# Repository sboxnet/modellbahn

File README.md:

# modellbahn

A project to supply code for my modellrailway.

Contains:
    
<h2>avr</h2>
code for ATMEL Microcontroller atxmega32a4u: Booster, Gleisbesetztmelder, Weichenservo, DCC Generator
<h2>kicad</h2>
schemas und layouts
<h2>libtmb++</h2>
library for programmer
<h2>programmer</h2>
programmer to program atmel xmega mcu's over PDI

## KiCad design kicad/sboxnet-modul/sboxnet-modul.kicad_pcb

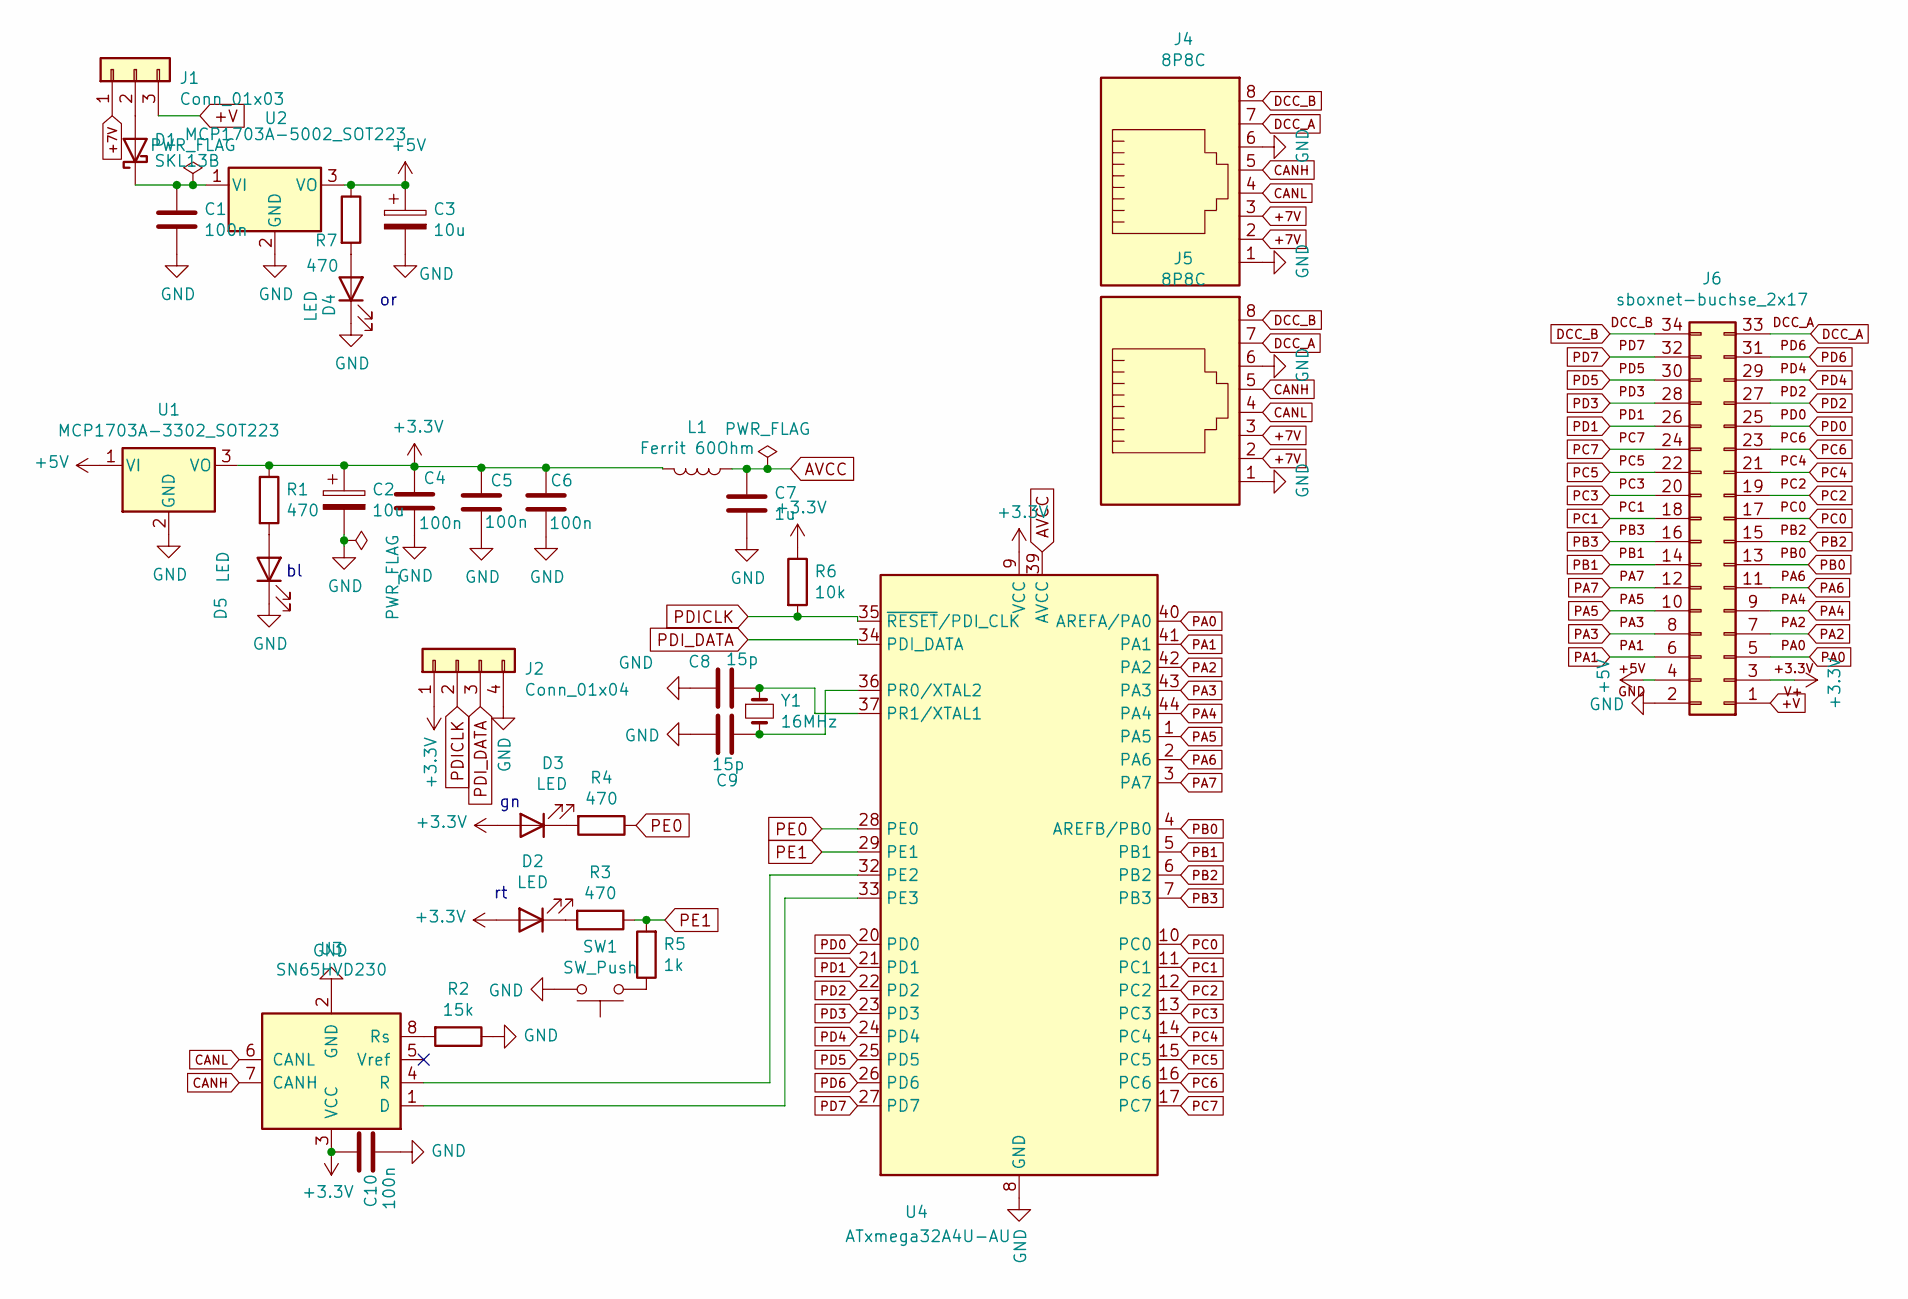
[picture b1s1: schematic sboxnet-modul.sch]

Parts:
C1, C4, C5, C6, C10: 100n; C_1206_3216Metric_Pad1.42x1.75mm_HandSolder
C2: 10u; C_1206_3216Metric_Pad1.42x1.75mm_HandSolder
C3: 10u; C_1206_3216Metric
C7: 1u; C_1206_3216Metric_Pad1.42x1.75mm_HandSolder
C8, C9: 15p; C_1206_3216Metric_Pad1.42x1.75mm_HandSolder
D1: SKL13B; D_SMB_Handsoldering
D2, D3, D4, D5: LED; LED_1206_3216Metric_Pad1.42x1.75mm_HandSolder
J1: Conn_01x03; PinHeader_1x03_P2.54mm_Vertical
J2: Conn_01x04; PinSocket_1x04_P2.54mm_Vertical
J4, J5: 8P8C; 8p8c-mebp
J6: sboxnet-buchse_2x17; sboxnet-buchse-2x17
L1: Ferrit 60Ohm; L_1206_3216Metric_Pad1.42x1.75mm_HandSolder
R1, R3, R4, R7: 470; R_1206_3216Metric_Pad1.42x1.75mm_HandSolder
R2: 15k; R_1206_3216Metric_Pad1.42x1.75mm_HandSolder
R5: 1k; R_1206_3216Metric_Pad1.42x1.75mm_HandSolder
R6: 10k; R_1206_3216Metric_Pad1.42x1.75mm_HandSolder
SW1: SW_Push; JTP-1130
U1: MCP1703A-3302_SOT223; SOT-223-3_TabPin2
U2: MCP1703A-5002_SOT223; SOT-223-3_TabPin2
U3: SN65HVD230; SOIC-8_3.9x4.9mm_P1.27mm
U4: ATxmega32A4U-AU; TQFP-44_10x10mm_P0.8mm
Y1: 16MHz; Crystal_HC49-U_Vertical

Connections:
+3V3: C2.1, C4.2, C5.2, C6.2, C10.2, D2.2 (A), D3.2 (A), J2.1, J6.3, L1.2, R1.1, R6.1, U1.3 (VO), U3.3 (VCC), U4.9 (VCC), U4.19 (VCC), U4.31 (VCC)
+5V: C3.1, J6.4, R7.1, U1.1 (VI), U2.3 (VO)
+7V: J1.1, J4.2, J4.3, J5.2, J5.3
+V: J1.3, J6.1
AVCC: C7.2, L1.1, U4.39 (AVCC)
CANH: J4.5, J5.5, U3.7 (CANH)
CANL: J4.4, J5.4, U3.6 (CANL)
DCC_A: J4.7, J5.7, J6.33
DCC_B: J4.8, J5.8, J6.34
GND: C1.1, C2.2, C3.2, C4.1, C5.1, C6.1, C7.1, C8.2, C9.2, C10.1, D4.1 (K), D5.1 (K), J2.4, J4.1, J4.6, J5.1, J5.6, J6.2, R2.1, SW1.2, U1.2 (GND), U2.2 (GND), U3.2 (GND), U4.8 (GND), U4.18 (GND), U4.30 (GND), U4.38 (GND)
unnamed: C1.2, D1.1 (K), U2.1 (VI)
unnamed: C8.1, U4.37 (PR1/XTAL1), Y1.1
unnamed: C9.1, U4.36 (PR0/XTAL2), Y1.2
unnamed: D1.2 (A), J1.2
unnamed: D2.1 (K), R3.2
unnamed: D3.1 (K), R4.2
unnamed: D4.2 (A), R7.2
unnamed: D5.2 (A), R1.2
unnamed: R2.2, U3.8 (Rs)
unnamed: R5.1, SW1.1
unnamed: U3.1 (D), U4.33 (PE3)
unnamed: U3.4 (R), U4.32 (PE2)
PA0: J6.5, U4.40 (AREFA/PA0)
PA1: J6.6, U4.41 (PA1)
PA2: J6.7, U4.42 (PA2)
PA3: J6.8, U4.43 (PA3)
PA4: J6.9, U4.44 (PA4)
PA5: J6.10, U4.1 (PA5)
PA6: J6.11, U4.2 (PA6)
PA7: J6.12, U4.3 (PA7)
PB0: J6.13, U4.4 (AREFB/PB0)
PB1: J6.14, U4.5 (PB1)
PB2: J6.15, U4.6 (PB2)
PB3: J6.16, U4.7 (PB3)
PC0: J6.17, U4.10 (PC0)
PC1: J6.18, U4.11 (PC1)
PC2: J6.19, U4.12 (PC2)
PC3: J6.20, U4.13 (PC3)
PC4: J6.21, U4.14 (PC4)
PC5: J6.22, U4.15 (PC5)
PC6: J6.23, U4.16 (PC6)
PC7: J6.24, U4.17 (PC7)
PD0: J6.25, U4.20 (PD0)
PD1: J6.26, U4.21 (PD1)
PD2: J6.27, U4.22 (PD2)
PD3: J6.28, U4.23 (PD3)
PD4: J6.29, U4.24 (PD4)
PD5: J6.30, U4.25 (PD5)
PD6: J6.31, U4.26 (PD6)
PD7: J6.32, U4.27 (PD7)
PDICLK: J2.2, R6.2, U4.35 (~RESET~/PDI_CLK)
PDI_DATA: J2.3, U4.34 (PDI_DATA)
PE0: R4.1, U4.28 (PE0)
PE1: R3.1, R5.2, U4.29 (PE1)

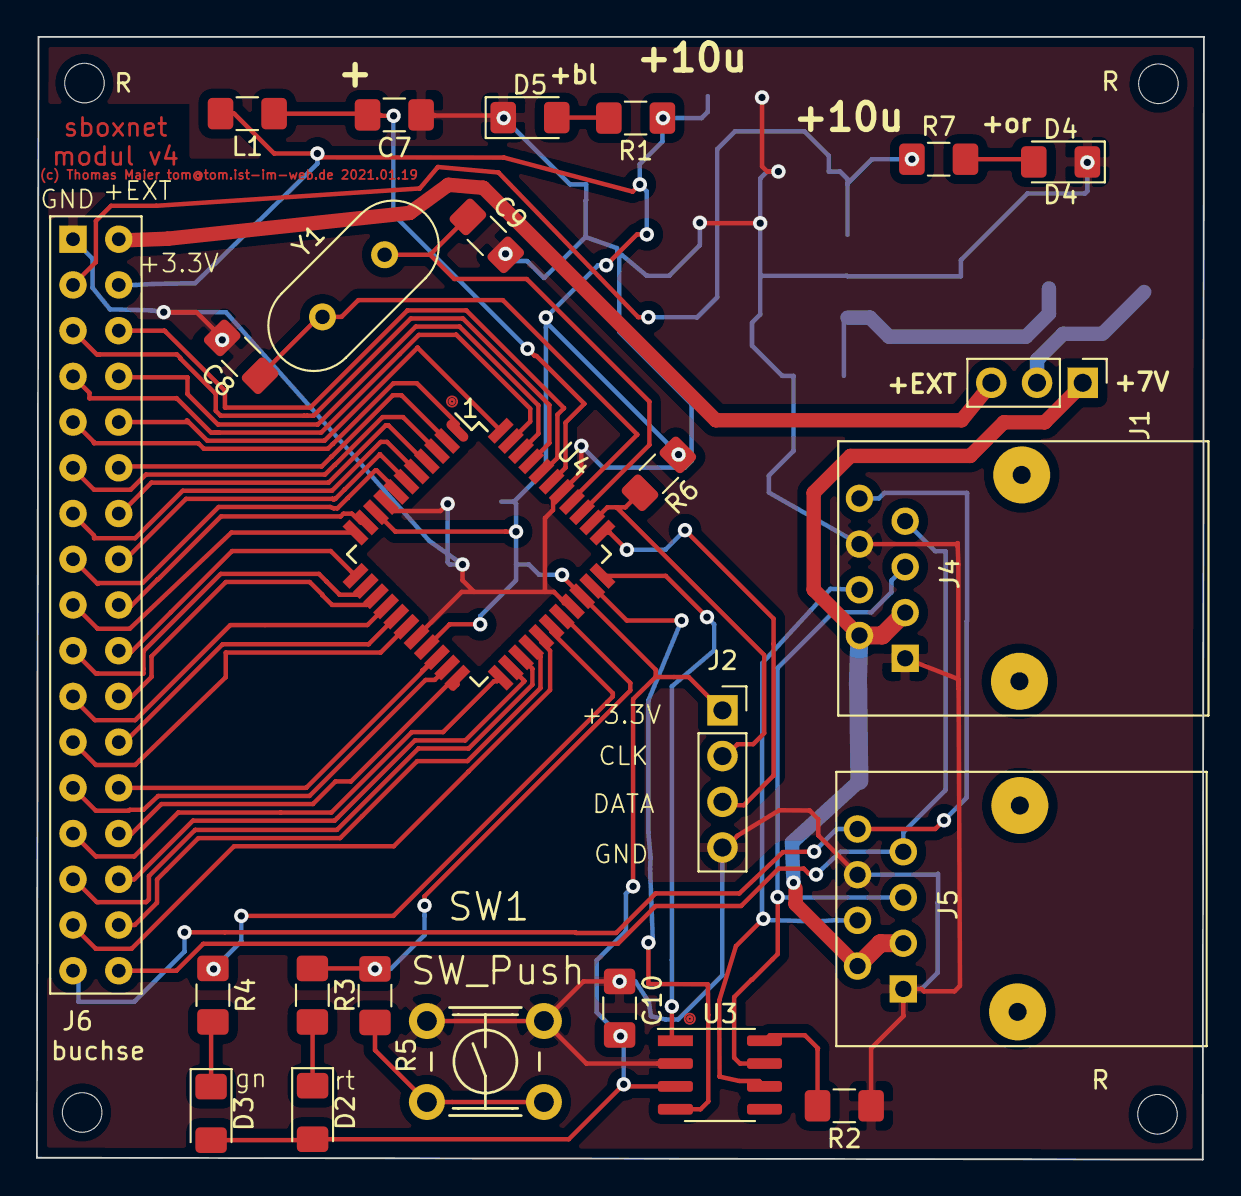
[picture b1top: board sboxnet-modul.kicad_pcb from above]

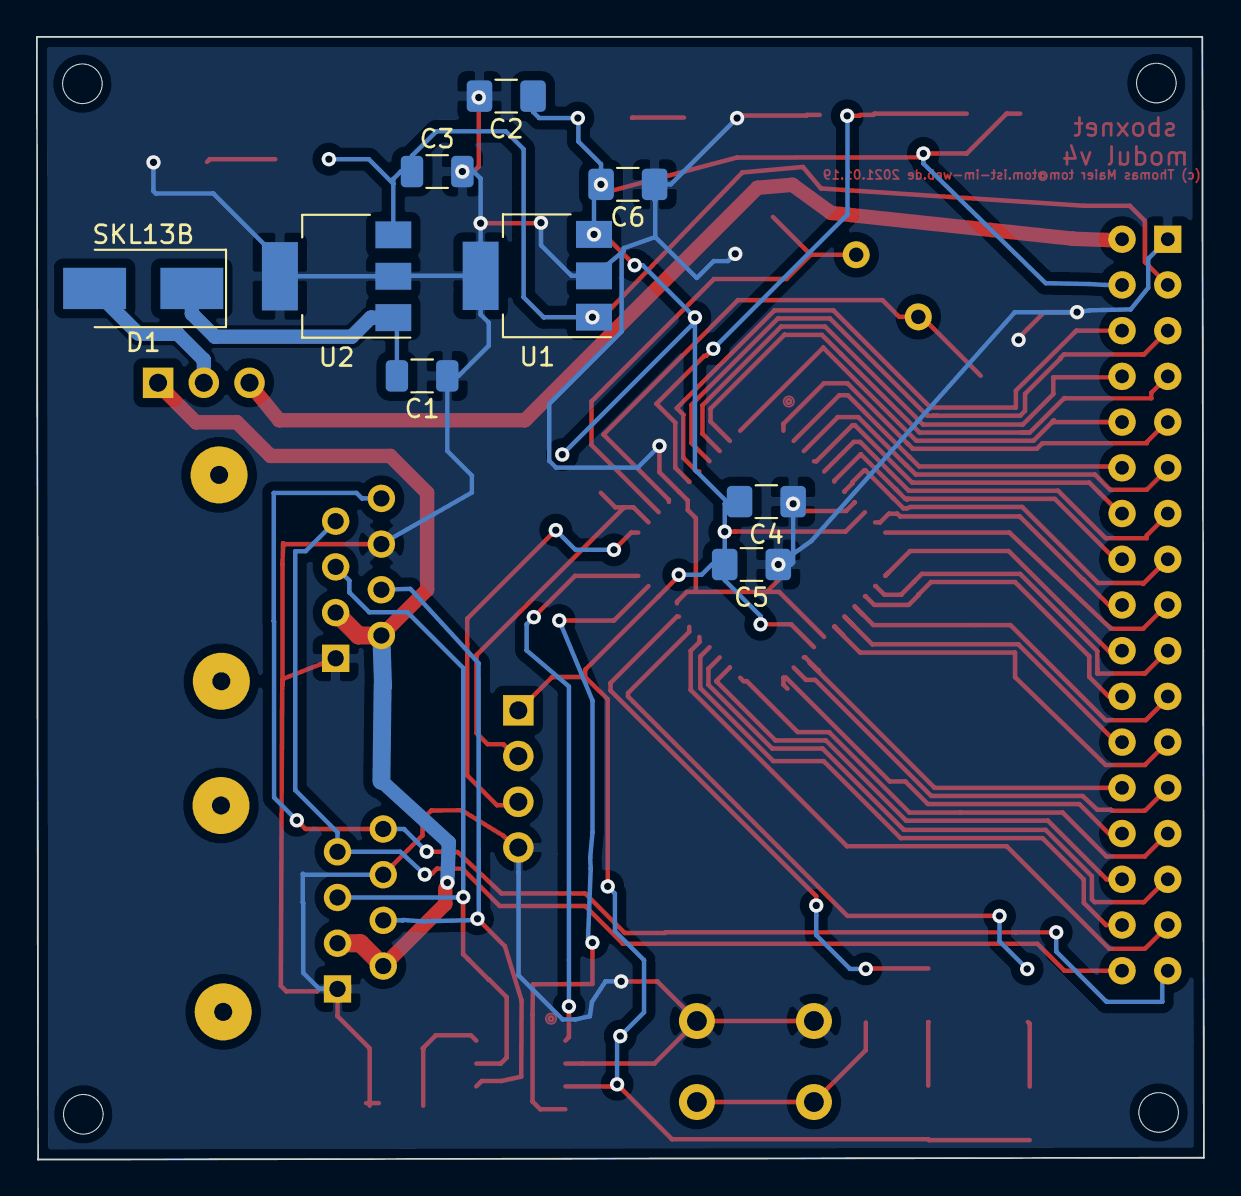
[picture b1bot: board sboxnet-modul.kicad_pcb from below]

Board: 2 copper layers, 64.8 x 62.4 mm, 38 parts (9 on the bottom side), 54 nets.

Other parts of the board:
R: MH2.2; MountingHole_2.2mm_M2
R#2, R#3: MH2.2; MountingHole_2.2mm_M2
buchse: MH2.2; MountingHole_2.2mm_M2

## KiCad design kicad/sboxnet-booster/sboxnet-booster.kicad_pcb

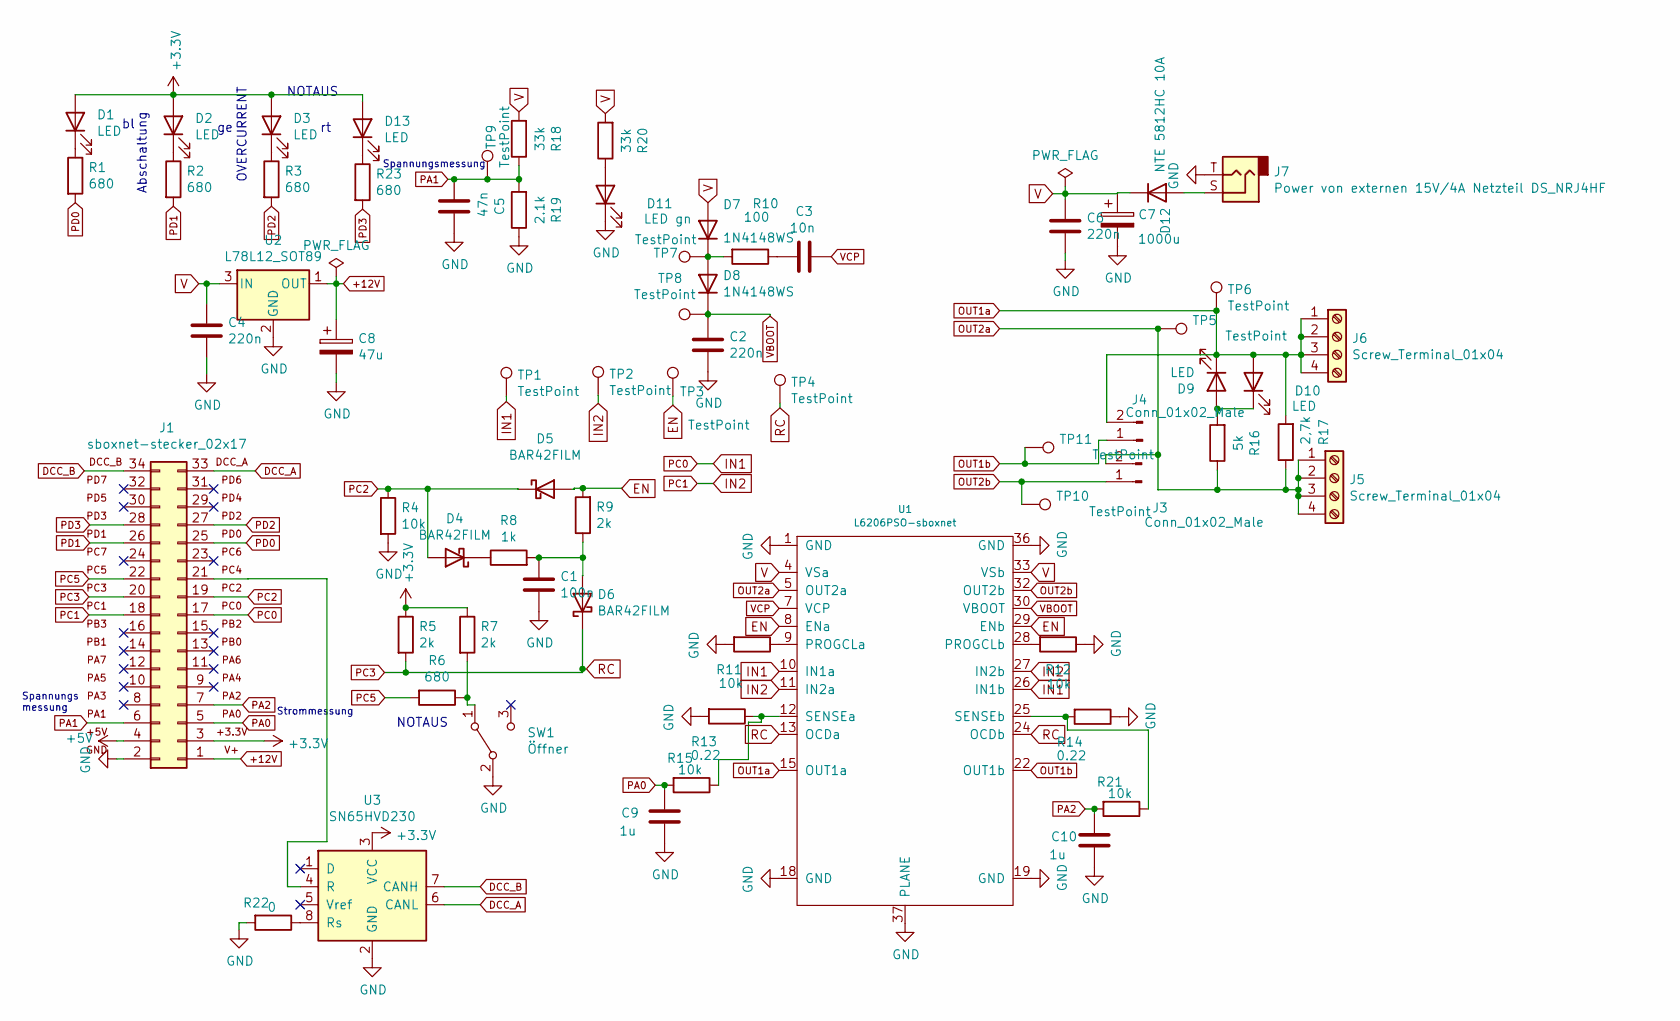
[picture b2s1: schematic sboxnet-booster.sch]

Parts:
C1: 100n; C_1206_3216Metric
C2, C4, C6: 220n; C_1206_3216Metric
C3: 10n; C_1206_3216Metric
C5: 47n; C_1206_3216Metric
C7: 1000u; CP_Radial_D12.5mm_P5.00mm
C8: 47u; CP_Radial_D5.0mm_P2.00mm
C9, C10: 1u; C_1206_3216Metric
D1, D2, D3, D9, D10, D13: LED; LED_D3.0mm
D4, D5, D6: BAR42FILM; SOT-23
D7, D8: 1N4148WS; D_SOD-323
D11: LED gn; LED_D3.0mm
D12: NTE 5812HC 10A; D_5W_P10.16mm_Horizontal
J1: sboxnet-stecker_02x17; sboxnet-stecker-2x17
J3, J4: Conn_01x02_Male; PinHeader_1x02_P2.54mm_Vertical
J5, J6: Screw_Terminal_01x04; TerminalBlock_Altech_AK300-4_P5.00mm
J7: Power von externen 15V/4A Netzteil DS_NRJ4HF; Jack_6.35mm_Neutrik_NRJ4HF_Horizontal
R1, R2, R3, R6, R23: 680; R_1206_3216Metric
R4, R11, R12, R15, R21: 10k; R_1206_3216Metric
R5, R7, R9: 2k; R_1206_3216Metric
R8: 1k; R_1206_3216Metric
R10: 100; R_1206_3216Metric
R13, R14: 0.22; R_Axial_Power_L38.0mm_W9.0mm_P45.72mm
R16: 5k; R_1206_3216Metric
R17: 2,7k; R_1206_3216Metric
R18, R20: 33k; R_1206_3216Metric
R19: 2.1k; R_1206_3216Metric
R22: 0; R_1206_3216Metric
SW1: Öffner; PinHeader_1x03_P2.54mm_Vertical
TP1, TP2, TP3, TP4, TP5, TP6, TP7, TP8, TP9, TP10, TP11: TestPoint; PinHeader_1x01_P2.54mm_Vertical
U1: L6206PSO-sboxnet; HSOP-36-1EP_11.0x15.9mm_P0.65mm_SlugDown_ThermalVias
U2: L78L12_SOT89; SOT-89-3
U3: SN65HVD230; SOIC-8_3.9x4.9mm_P1.27mm

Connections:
+3V3: D1.2 (A), D2.2 (A), D3.2 (A), D13.2 (A), J1.3, R5.1, R7.1, U3.3 (VCC)
+5V: J1.4
+12V: C8.1, J1.1, U2.1 (OUT)
DCC_A: J1.33, U3.6 (CANL)
DCC_B: J1.34, U3.7 (CANH)
EN: D5.1 (A), R9.2, TP3.1, U1.8 (ENa), U1.29 (ENb)
GND: C1.2, C2.1, C4.1, C5.1, C6.1, C7.2, C8.2, C9.1, C10.1, D11.1 (K), J1.2, J7.T, R4.2, R11.2, R12.1, R13.2, R14.1, R19.1, R22.2, SW1.2 (B), U1.1 (GND), U1.18 (GND), U1.19 (GND), U1.36 (GND), U1.37 (PLANE), U2.2 (GND), U3.2 (GND)
IN1: J1.17, TP1.1, U1.10 (IN1a), U1.26 (IN1b)
IN2: J1.18, TP2.1, U1.11 (IN2a), U1.27 (IN2b)
unnamed: C1.1, D6.1 (A), R8.2, R9.1
unnamed: C3.2, R10.1
unnamed: D1.1 (K), R1.1
unnamed: D2.1 (K), R2.1
unnamed: D3.1 (K), R3.1
unnamed: D4.3 (K), R8.1
unnamed: D7.1 (K), D8.2 (A), R10.2, TP7.1
unnamed: D9.2 (A), D10.1 (K), R16.2
unnamed: D11.2 (A), R20.1
unnamed: D12.2 (A), J7.S
unnamed: D13.1 (K), R23.1
unnamed: J1.21, U3.4 (R)
unnamed: R6.1, R7.2, SW1.1 (A)
unnamed: R11.1, U1.9 (PROGCLa)
unnamed: R12.2, U1.28 (PROGCLb)
unnamed: R13.1, R15.1, U1.12 (SENSEa)
unnamed: R14.2, R21.1, U1.25 (SENSEb)
unnamed: R22.1, U3.8 (Rs)
OUT1a: D9.1 (K), D10.2 (A), J4.2, J6.1, J6.2, J6.3, J6.4, R17.2, TP6.1, U1.15 (OUT1a)
OUT1b: J4.1, TP11.1, U1.22 (OUT1b)
OUT2a: J3.2, J5.1, J5.2, J5.3, J5.4, R16.1, R17.1, TP5.1, U1.5 (OUT2a)
OUT2b: J3.1, TP10.1, U1.32 (OUT2b)
PA0: C9.2, J1.5, R15.2
PA1: C5.2, J1.6, R18.1, R19.2, TP9.1
PA2: C10.2, J1.7, R21.2
PC2: D4.1 (A), D5.3 (K), J1.19, R4.1
PC3: D6.3 (K), J1.20, R5.2, TP4.1, U1.13 (OCDa), U1.24 (OCDb)
PC5: J1.22, R6.2
PD0: J1.25, R1.2
PD1: J1.26, R2.2
PD2: J1.27, R3.2
PD3: J1.28, R23.2
V: C4.2, C6.2, C7.1, D7.2 (A), D12.1 (K), R18.2, R20.2, U1.4 (VSa), U1.33 (VSb), U2.3 (IN)
VBOOT: C2.2, D8.1 (K), TP8.1, U1.30 (VBOOT)
VCP: C3.1, U1.7 (VCP)

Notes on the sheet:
NOTAUS
OVERCURRENT
Abschaltung
Spannungsmessung
Spannungs messung
Strommessung

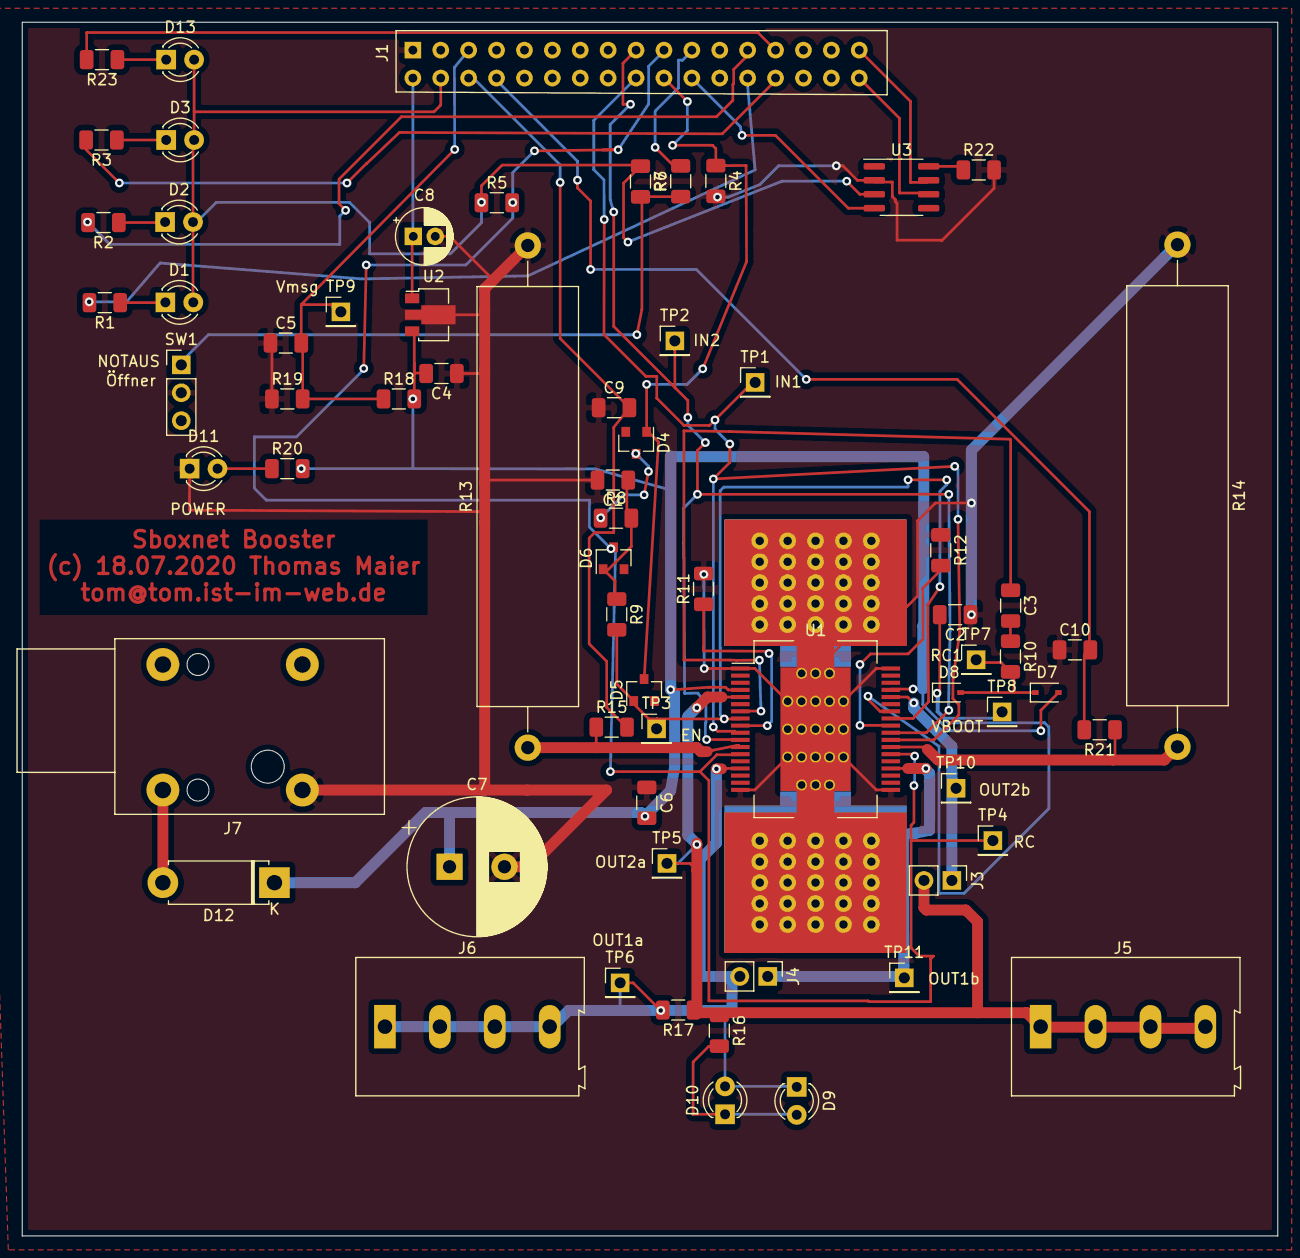
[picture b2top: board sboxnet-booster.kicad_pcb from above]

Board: 2 copper layers, 114.3 x 110.5 mm, 67 parts (0 on the bottom side), 43 nets.

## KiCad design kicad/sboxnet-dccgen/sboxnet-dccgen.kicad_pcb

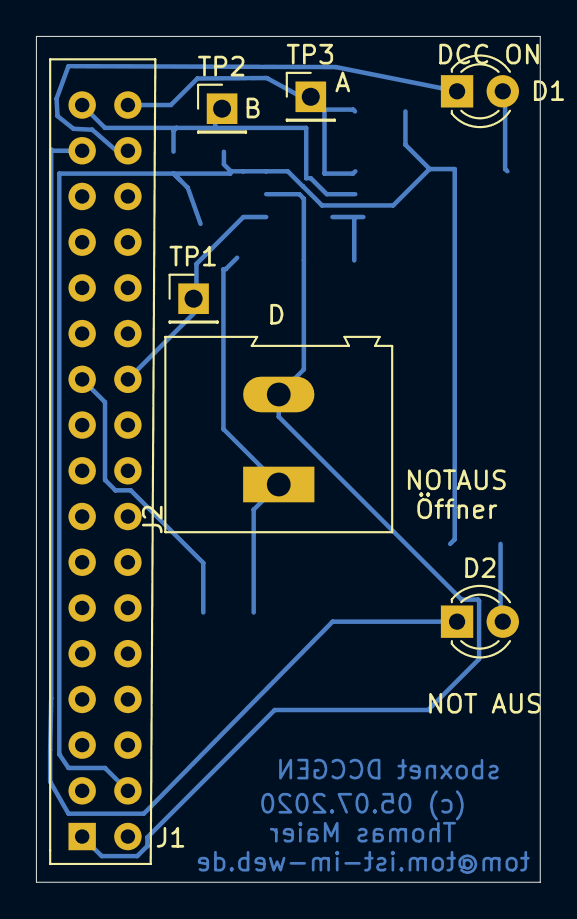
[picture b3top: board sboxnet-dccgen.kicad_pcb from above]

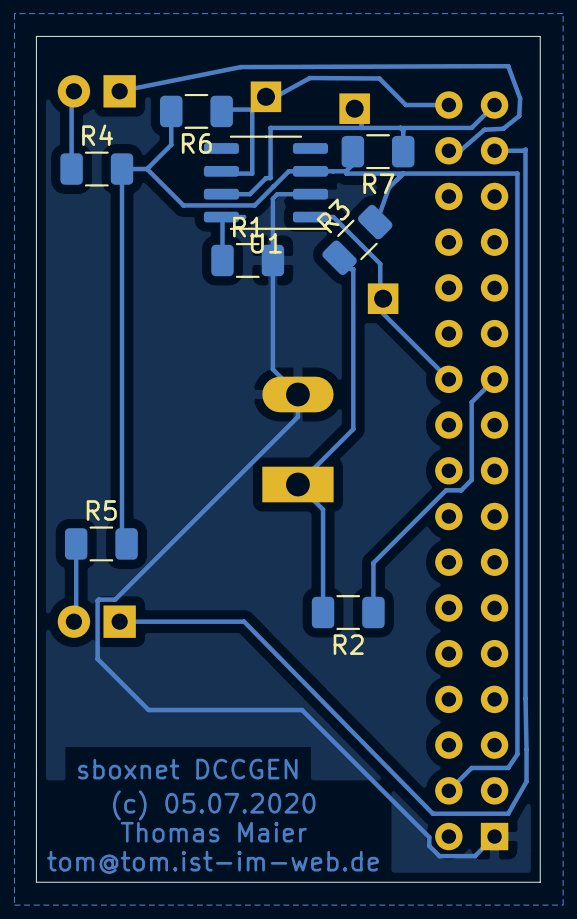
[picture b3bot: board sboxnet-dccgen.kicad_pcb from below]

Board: 2 copper layers, 28.0 x 47.0 mm, 15 parts (8 on the bottom side), 12 nets.

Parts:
D1, D2: LED; LED_D3.0mm
J1: sboxnet-stecker_02x17; sboxnet-stecker-2x17
J2: Screw_Terminal_01x02; TerminalBlock_Altech_AK300-2_P5.00mm
R1: 0; R_1206_3216Metric
R2, R4, R5: 680; R_1206_3216Metric
R3: 2,2k; R_1206_3216Metric
R6, R7: 120; R_1206_3216Metric
TP1, TP2, TP3: TestPoint; PinHeader_1x01_P2.54mm_Vertical
U1: SN65HVD230; SOIC-8_3.9x4.9mm_P1.27mm

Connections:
+3V3: J1.3, R3.2, R4.2, R5.2, R6.2, R7.2, U1.3
D: J1.21, TP1.1, U1.1
DCC_A: J1.33, R6.1, TP3.1, U1.6
DCC_B: J1.34, R7.1, TP2.1, U1.7
GND: J1.2, J2.2, R1.2, U1.2
unnamed: D1.2, R4.1
unnamed: D2.2, R5.1
unnamed: J2.1, R2.2, R3.1
unnamed: R1.1, U1.8
Notaus: J1.22, R2.1
PD6: D1.1, J1.31
PD7: D2.1, J1.32

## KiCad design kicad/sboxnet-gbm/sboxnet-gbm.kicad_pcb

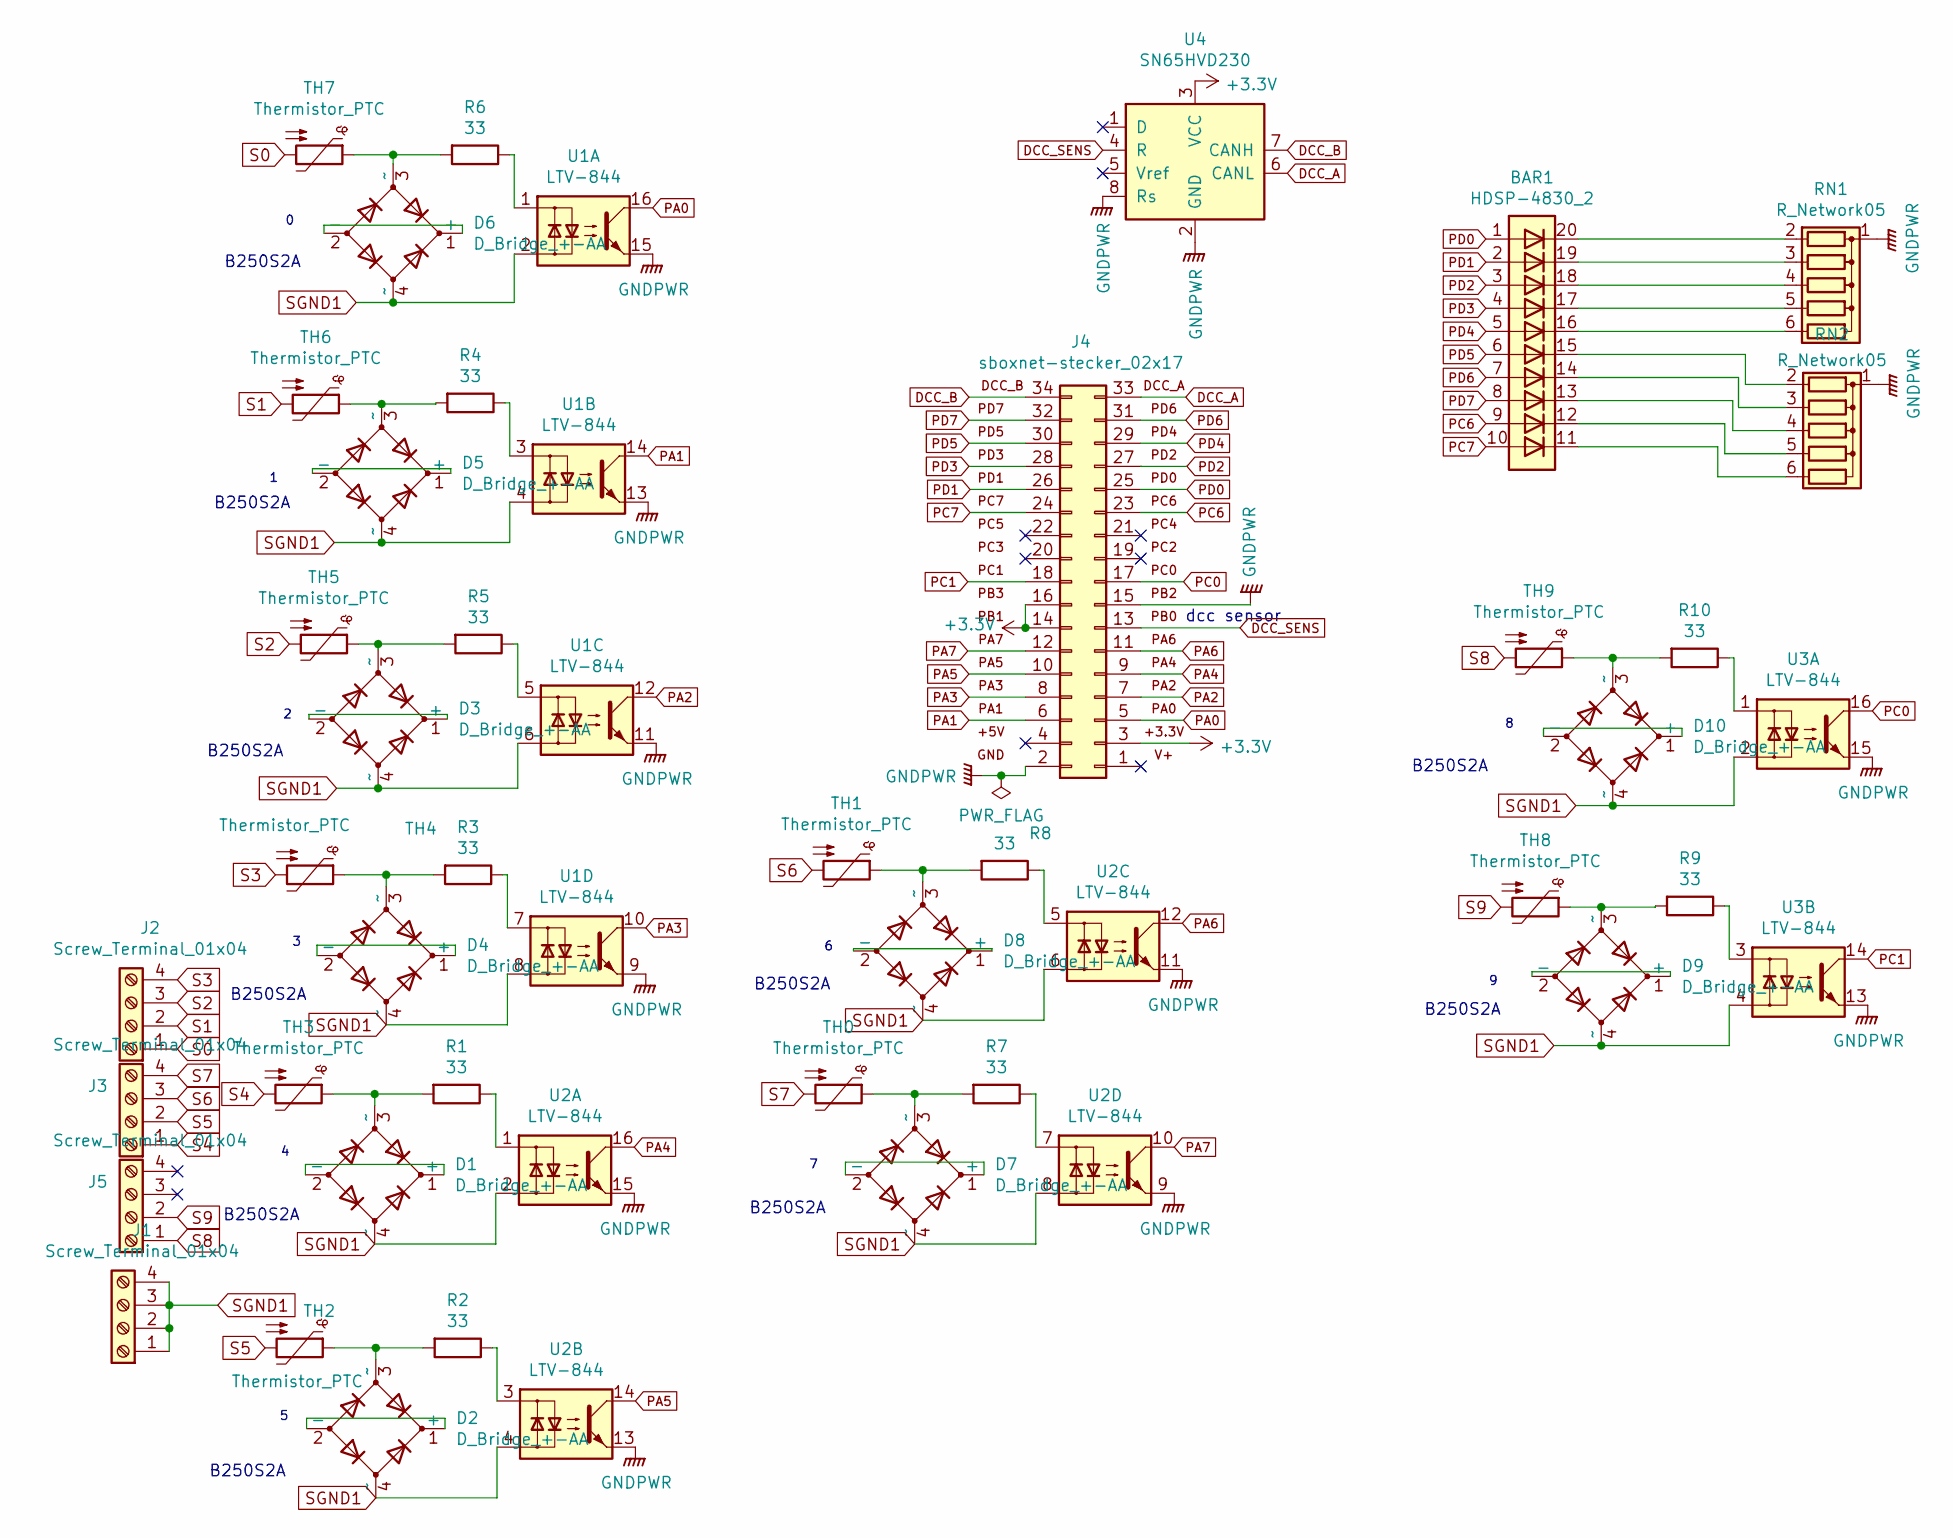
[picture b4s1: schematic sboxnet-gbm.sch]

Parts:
BAR1: HDSP-4830_2; HDSP-4830
D1, D2, D3, D4, D5, D6, D7, D8, D9, D10: D_Bridge_+-AA; Diode_Bridge_Diotec_SO-DIL-Slim
J1, J2, J3, J5: Screw_Terminal_01x04; TerminalBlock_Altech_AK300-4_P5.00mm
J4: sboxnet-stecker_02x17; sboxnet-stecker-2x17
R1, R2, R3, R4, R5, R6, R7, R8, R9, R10: 33; R_1206_3216Metric_Pad1.42x1.75mm_HandSolder
RN1, RN2: R_Network05; R_Array_SIP6
TH0, TH1, TH2, TH3, TH4, TH5, TH6, TH7, TH8, TH9: Thermistor_PTC; R_1206_3216Metric
U1, U2, U3: LTV-844; DIP-16_W7.62mm
U4: SN65HVD230; SOIC-8_3.9x4.9mm_P1.27mm

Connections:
+3V3: J4.3, J4.14, J4.16, U4.3 (VCC)
DCC_A: J4.33, U4.6 (CANL)
DCC_B: J4.34, U4.7 (CANH)
DCC_SENS: J4.13, U4.4 (R)
GNDPWR: J4.2, J4.15, RN1.1 (common), RN2.1 (common), U1.9, U1.11, U1.13, U1.15, U2.9, U2.11, U2.13, U2.15, U3.13, U3.15, U4.2 (GND), U4.8 (Rs)
unnamed: BAR1.11 (K), RN2.6 (R5)
unnamed: BAR1.12 (K), RN2.5 (R4)
unnamed: BAR1.13 (K), RN2.4 (R3)
unnamed: BAR1.14 (K), RN2.3 (R2)
unnamed: BAR1.15 (K), RN2.2 (R1)
unnamed: BAR1.16 (K), RN1.6 (R5)
unnamed: BAR1.17 (K), RN1.5 (R4)
unnamed: BAR1.18 (K), RN1.4 (R3)
unnamed: BAR1.19 (K), RN1.3 (R2)
unnamed: BAR1.20 (K), RN1.2 (R1)
unnamed: D1.1 (+), D1.2 (-)
unnamed: D1.3 (~~), R1.2, TH3.1
unnamed: D2.1 (+), D2.2 (-)
unnamed: D2.3 (~~), R2.2, TH2.1
unnamed: D3.1 (+), D3.2 (-)
unnamed: D3.3 (~~), R5.2, TH5.1
unnamed: D4.1 (+), D4.2 (-)
unnamed: D4.3 (~~), R3.2, TH4.1
unnamed: D5.1 (+), D5.2 (-)
unnamed: D5.3 (~~), R4.2, TH6.1
unnamed: D6.1 (+), D6.2 (-)
unnamed: D6.3 (~~), R6.2, TH7.1
unnamed: D7.1 (+), D7.2 (-)
unnamed: D7.3 (~~), R7.2, TH0.1
unnamed: D8.1 (+), D8.2 (-)
unnamed: D8.3 (~~), R8.2, TH1.1
unnamed: D9.1 (+), D9.2 (-)
unnamed: D9.3 (~~), R9.2, TH8.1
unnamed: D10.1 (+), D10.2 (-)
unnamed: D10.3 (~~), R10.2, TH9.1
unnamed: R1.1, U2.1
unnamed: R2.1, U2.3
unnamed: R3.1, U1.7
unnamed: R4.1, U1.3
unnamed: R5.1, U1.5
unnamed: R6.1, U1.1
unnamed: R7.1, U2.7
unnamed: R8.1, U2.5
unnamed: R9.1, U3.3
unnamed: R10.1, U3.1
PA0: J4.5, U1.16; also elsewhere on the board
PA1: J4.6, U1.14
PA2: J4.7, U1.12
PA3: J4.8, U1.10
PA4: J4.9, U2.16
PA5: J4.10, U2.14
PA6: J4.11, U2.12
PA7: J4.12, U2.10
PC0: J4.17, U3.16
PC1: J4.18, U3.14
PC6: BAR1.9 (A), J4.23
PC7: BAR1.10 (A), J4.24
PD0: BAR1.1 (A), J4.25
PD1: BAR1.2 (A), J4.26
PD2: BAR1.3 (A), J4.27
PD3: BAR1.4 (A), J4.28
PD4: BAR1.5 (A), J4.29
PD5: BAR1.6 (A), J4.30
PD6: BAR1.7 (A), J4.31
PD7: BAR1.8 (A), J4.32 (PD7)
S0: J2.1, TH7.2
S1: J2.2, TH6.2
S2: J2.3, TH5.2
S3: J2.4, TH4.2
S4: J3.1, TH3.2
S5: J3.2, TH2.2
S6: J3.3, TH1.2
S7: J3.4, TH0.2
S8: J5.1, TH9.2
S9: J5.2, TH8.2
SGND1: D1.4 (~~), D2.4 (~~), D3.4 (~~), D4.4 (~~), D5.4 (~~), D6.4 (~~), D7.4 (~~), D8.4 (~~), D9.4 (~~), D10.4 (~~), J1.1, J1.2, J1.3, J1.4, U1.2, U1.4, U1.6, U1.8, U2.2, U2.4, U2.6, U2.8, U3.2, U3.4

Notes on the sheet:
B250S2A
dcc sensor

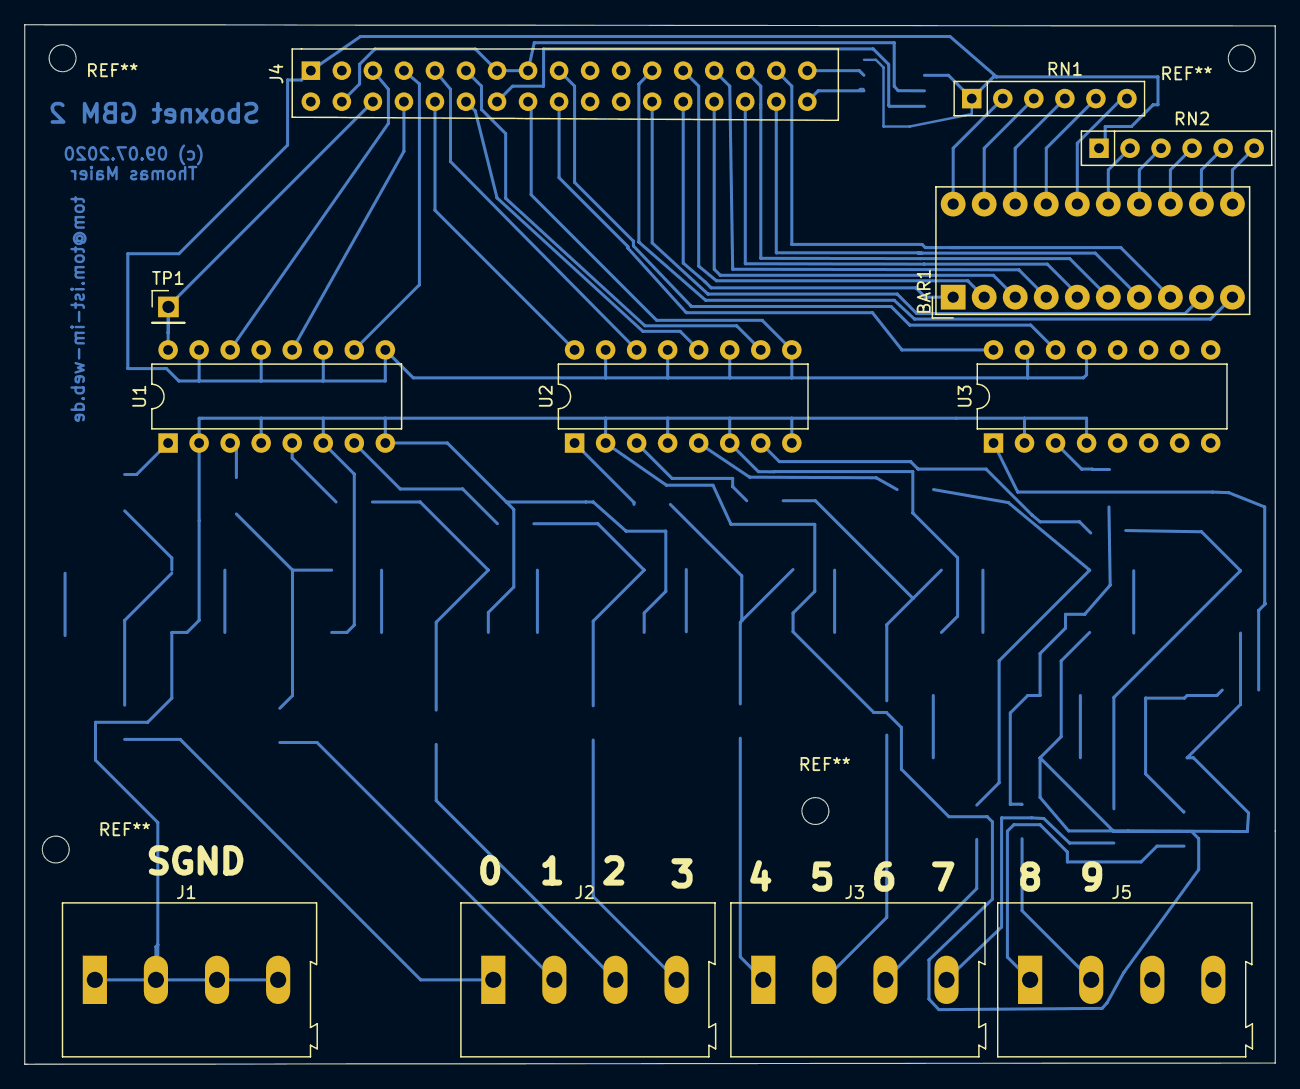
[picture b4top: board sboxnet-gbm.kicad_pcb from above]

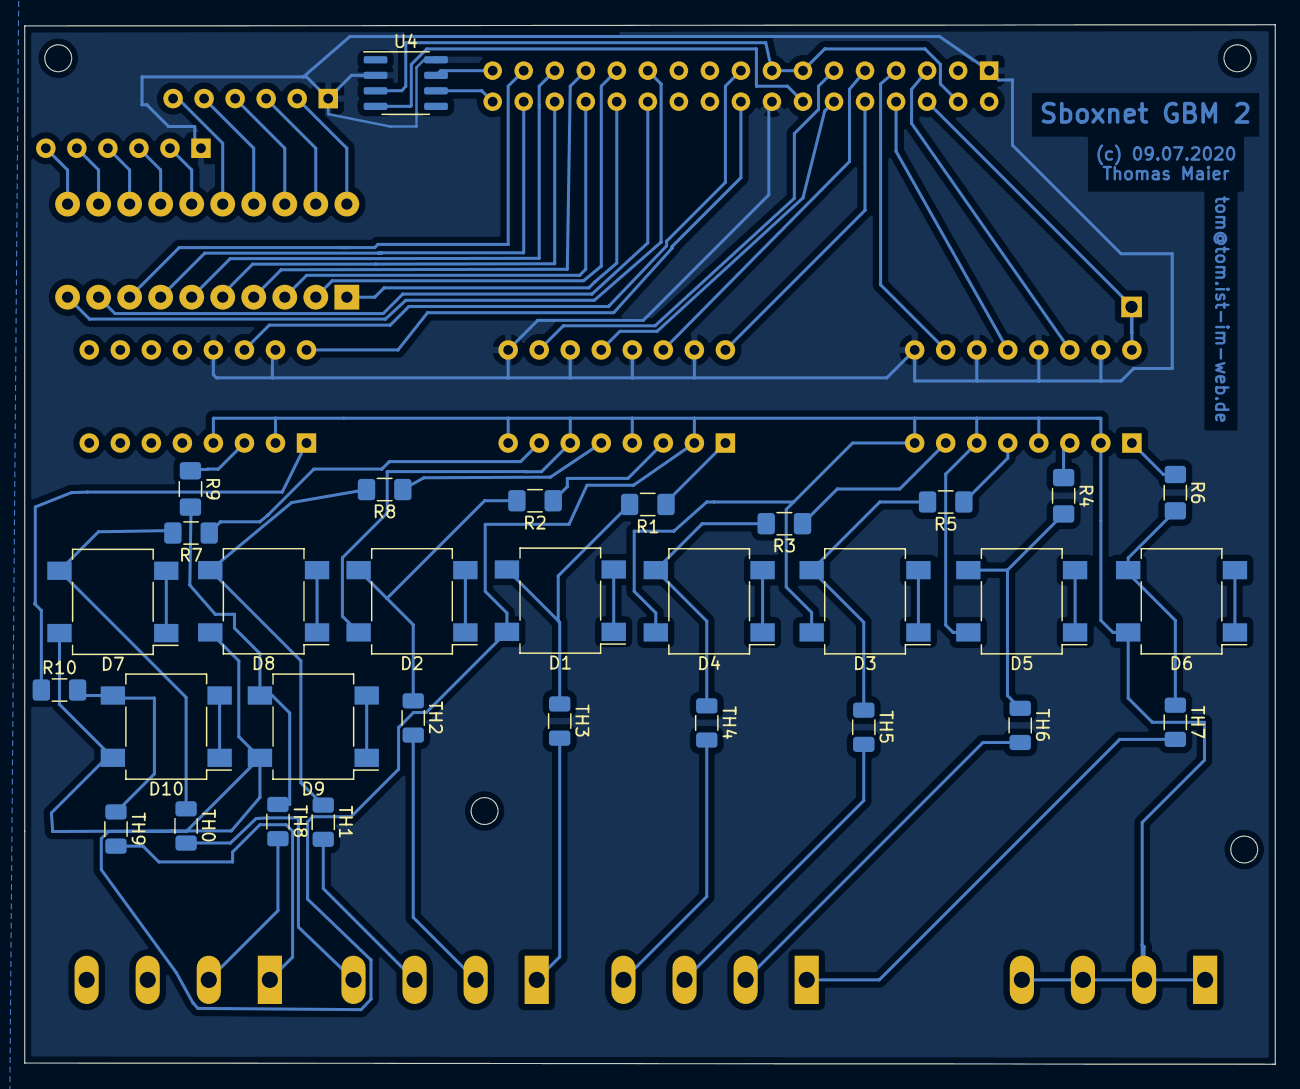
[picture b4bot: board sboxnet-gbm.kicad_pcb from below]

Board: 2 copper layers, 102.4 x 85.1 mm, 43 parts (31 on the bottom side), 76 nets.

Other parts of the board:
TP1: TestPoint; PinHeader_1x01_P2.54mm_Vertical

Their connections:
PA0: TP1.1; also elsewhere on the board

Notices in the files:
avr/sboxnet/sb3/booster.c:
Copyright (C) 2014-2015
Copyright: See COPYING file that comes with this distribution
This program is free software; you can redistribute it and/or modify
it under the terms of the GNU General Public License as published by
the Free Software Foundation; either version 2 of the License, or
(at your option) any later version.
avr/sboxnet/sb3/gbmelder.c:
Copyright (C) 2014-2020
kicad/gpio-usb/gpio-usb.sch:
Thomas Maier  (c) 2013-2015
